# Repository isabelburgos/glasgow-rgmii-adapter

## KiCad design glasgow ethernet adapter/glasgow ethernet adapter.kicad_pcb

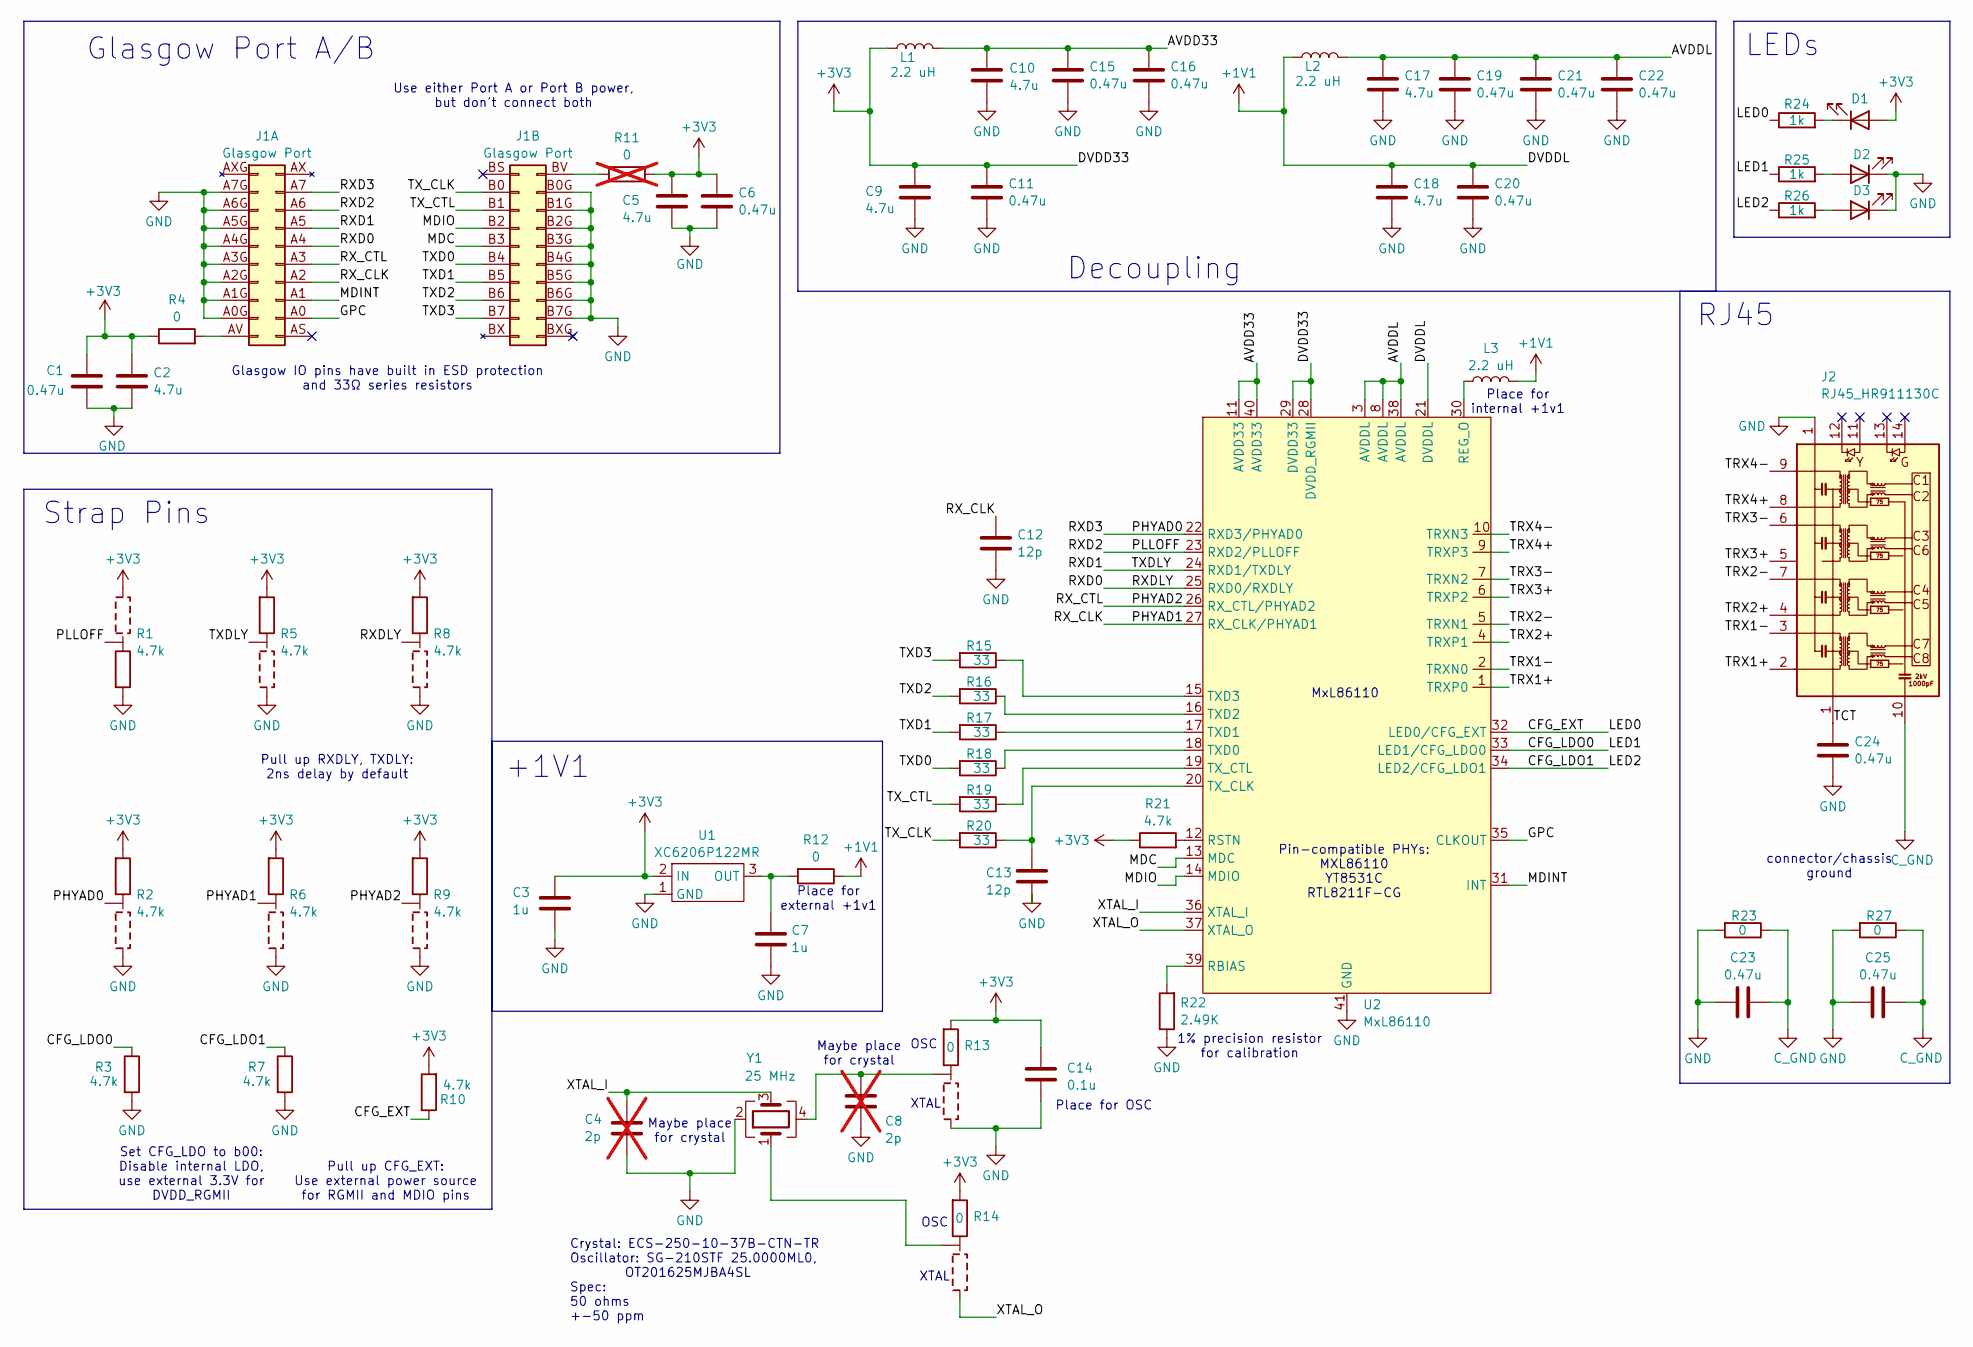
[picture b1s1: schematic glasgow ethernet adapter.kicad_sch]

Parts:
C1, C6, C11, C15, C16, C19, C20, C21, C22, C23, C24, C25: 0.47u; C_0402_1005Metric; JLC Part ID C967572
C2, C5, C9, C10, C17, C18: 4.7u; C_1206_3216Metric; JLC Part ID C29823
C3, C7: 1u; C_0603_1608Metric; JLC Part ID C1592
C4, C8: 2p; C_0402_1005Metric; not fitted
C12, C13: 12p; C_0402_1005Metric; JLC Part ID C1547
C14: 0.1u; C_0402_1005Metric; JLC Part ID C1525
D1: LED_0; D_0603_1608Metric; JLC Part ID C111340
D2: LED_1; D_0603_1608Metric; JLC Part ID C83904
D3: LED_2; D_0603_1608Metric; JLC Part ID C2977076
J1: Glasgow Port; Glasgow; JLC Part ID C124419
J2: RJ45_HR911130C; HR911130C_HAN; JLC Part ID C50933
L1, L2, L3: 2.2 uH; L_0603_1608Metric; JLC Part ID C17305
R1, R2, R5, R6, R8, R9: 4.7k; R-3-Way_0402_1005Metric; JLC Part ID C25900
R3, R7, R10, R21: 4.7k; R_0402_1005Metric; JLC Part ID C25900
R4: 0; R_0603_1608Metric; JLC Part ID C17168
R11: 0; R_0603_1608Metric; JLC Part ID C21189; not fitted
R12: 0; R_0603_1608Metric; JLC Part ID C15402
R13, R14: 0; R-3-Way_0402_1005Metric; JLC Part ID C17168
R15, R16, R17, R18, R19, R20: 33; R_0402_1005Metric; JLC Part ID C25105
R22: 2.49K; R_0402_1005Metric; JLC Part ID C102924
R23, R27: 0; R_0402_1005Metric; JLC Part ID C17168
R24, R25, R26: 1k; R_0402_1005Metric; JLC Part ID C173697
U1: XC6206P122MR; SOT-23; JLC Part ID C2827649
U2: MxL86110; QFN-40-1EP_5x5mm_P0.4mm_EP3.8x3.8mm; JLC Part ID C187932
Y1: 25 MHz; XTAL_ECS-160-9-37-CKM-TR; JLC Part ID C669080

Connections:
+1V1: C18.1, C20.1, L2.1, L3.2, R12.1, U2.21 (DVDDL)
+3V3: C1.1, C2.1, C3.1, C5.1, C6.1, C9.1, C11.1, C14.1, D1.2 (A), L1.1, R1.3, R2.1, R4.1, R5.1, R6.1, R8.1, R9.1, R10.2, R11.1, R13.1, R14.1, R21.1, U1.2 (IN), U2.28 (DVDD_RGMII), U2.29 (DVDD33)
/AVDD33: C10.1, C15.1, C16.1, L1.2, U2.11 (AVDD33), U2.40 (AVDD33)
/AVDDL: C17.1, C19.1, C21.1, C22.1, L2.2, U2.3 (AVDDL), U2.8 (AVDDL), U2.38 (AVDDL)
/CFG_EXT: R10.1, R24.1, U2.32 (LED0/CFG_EXT)
/CFG_LDO0: R3.1, R25.1, U2.33 (LED1/CFG_LDO0)
/CFG_LDO1: R7.1, R26.1, U2.34 (LED2/CFG_LDO1)
/GPC: J1.A0, U2.35 (CLKOUT)
/MDC: J1.B3, U2.13 (MDC)
/MDINT: J1.A1, U2.31 (INT)
/MDIO: J1.B2, U2.14 (MDIO)
/PHYAD0: J1.A7, R2.2, U2.22 (RXD3/PHYAD0)
/PHYAD1: C12.1, J1.A2, R6.2, U2.27 (RX_CLK/PHYAD1)
/PHYAD2: J1.A3, R9.2, U2.26 (RX_CTL/PHYAD2)
/PLLOFF: J1.A6, R1.2, U2.23 (RXD2/PLLOFF)
/RXD0: J1.A4, R8.2, U2.25 (RXD0/RXDLY)
/RXD1: J1.A5, R5.2, U2.24 (RXD1/TXDLY)
/TRX1+: J2.2 (0+), U2.1 (TRXP0)
/TRX1-: J2.3 (0-), U2.2 (TRXN0)
/TRX2+: J2.4 (1+), U2.4 (TRXP1)
/TRX2-: J2.7 (1-), U2.5 (TRXN1)
/TRX3+: J2.5 (2+), U2.6 (TRXP2)
/TRX3-: J2.6 (2-), U2.7 (TRXN2)
/TRX4+: J2.8 (3+), U2.9 (TRXP3)
/TRX4-: J2.9 (3-), U2.10 (TRXN3)
/TXD0: J1.B4, R18.2
/TXD1: J1.B5, R17.2
/TXD2: J1.B6, R16.2
/TXD3: J1.B7, R15.2
/TX_CLK: J1.B0, R20.2
/TX_CTL: J1.B1, R19.2
/XTAL_I: C4.1, U2.36 (XTAL_I), Y1.3
/XTAL_O: R14.3, U2.37 (XTAL_O)
C_GND: C23.1, C25.1, J2.10 (SH), R23.1, R27.1
unnamed: C8.1, R13.2, Y1.4
unnamed: D1.1 (K), R24.2
unnamed: D2.2 (A), R25.2
unnamed: D3.2 (A), R26.2
unnamed: J1.AV, R4.2
unnamed: J1.BV, R11.2
unnamed: R14.2, Y1.1
unnamed: C7.1, R12.2, U1.3 (OUT)
unnamed: R22.2, U2.39 (RBIAS)
unnamed: L3.1, U2.30 (REG_O)
unnamed: R21.2, U2.12 (RSTN)
unnamed: R18.1, U2.18 (TXD0)
unnamed: R17.1, U2.17 (TXD1)
unnamed: R16.1, U2.16 (TXD2)
unnamed: R15.1, U2.15 (TXD3)
unnamed: C13.1, R20.1, U2.20 (TX_CLK)
unnamed: R19.1, U2.19 (TX_CTL)

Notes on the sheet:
Place for external +1v1
OSC
Strap Pins
Maybe place for crystal
MxL86110
Pull up RXDLY, TXDLY: 2ns delay by default
Use either Port A or Port B power, but don't connect both
connector/chassis ground
Set CFG_LDO to b00: Disable internal LDO, use external 3.3V for DVDD_RGMII
Pull up CFG_EXT: Use external power source for RGMII and MDIO pins
+1V1
XTAL
Place for OSC
1% precision resistor for calibration
Decoupling
Pin-compatible PHYs: MXL86110 YT8531C RTL8211F-CG
Place for internal +1v1
Glasgow Port A/B
RJ45
Glasgow IO pins have built in ESD protection and 33Ω series resistors
Crystal: ECS-250-10-37B-CTN-TR Oscillator: SG-210STF 25.0000ML0, OT201625MJBA4SL Spec: 50 ohms +-50 ppm
LEDs

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
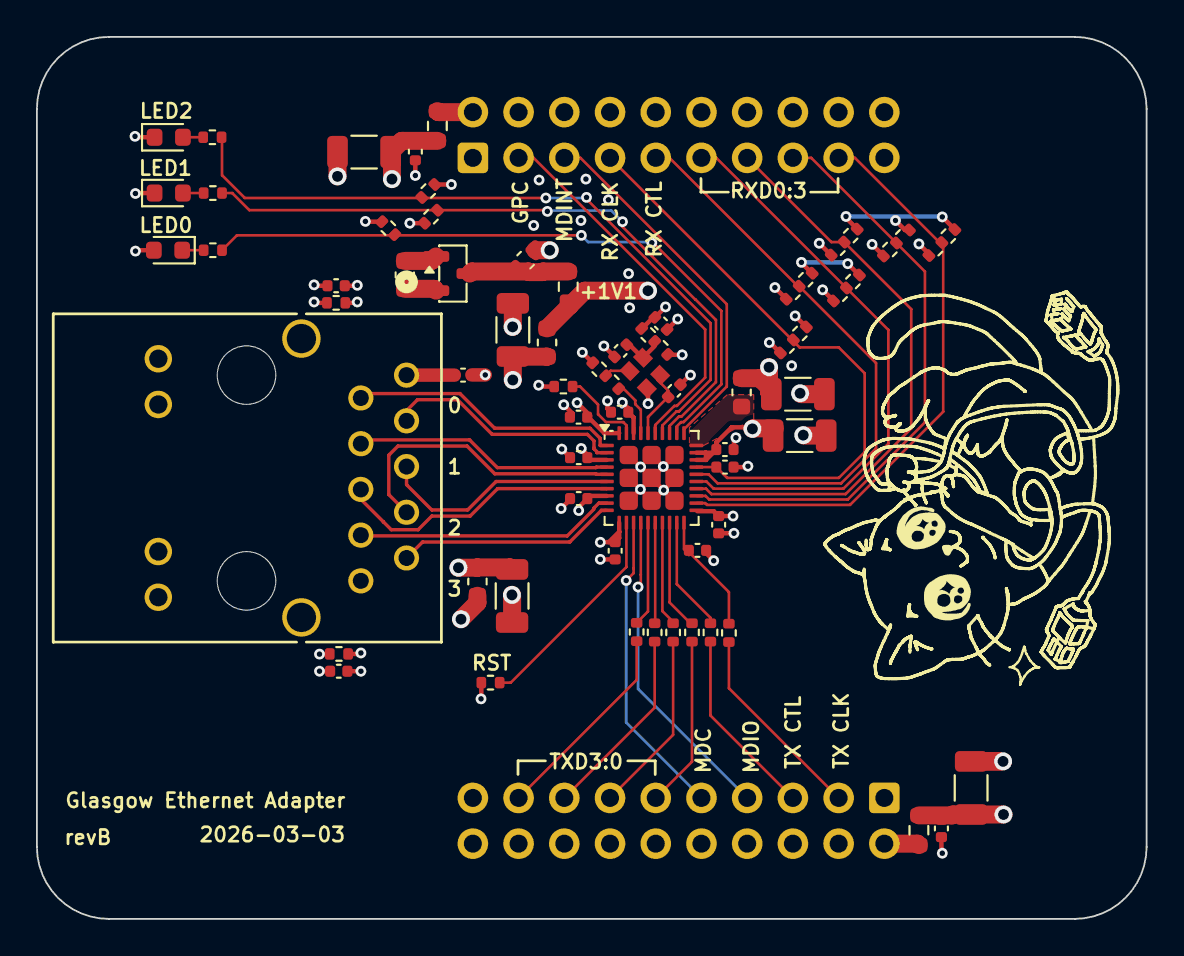
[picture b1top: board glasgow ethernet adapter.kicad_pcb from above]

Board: 4 copper layers, 61.7 x 49.0 mm, 63 parts (0 on the bottom side), 53 nets.

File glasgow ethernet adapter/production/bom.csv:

Designator,Footprint,Quantity,Value,JLC Part #
"C1, C11, C15, C16, C19, C20, C21, C22, C23, C24, C25, C6",0402,12,0.47u,C967572
"C10, C17, C18, C2, C5, C9",1206,6,4.7u,C29823
"C12, C13",0402,2,12p,C1547
C14,0402,1,0.1u,C1525
"C3, C7",0603,2,1u,C1592
D1,0603,1,LED_0,C111340
D2,0603,1,LED_1,C83904
D3,0603,1,LED_2,C2977076
J1A,Conn_2x10,1,B-2200S20P-B120,C124419
J1B,Conn_2x10,1,B-2200S20P-B120,C124419
J2,HR911130C_HAN,1,RJ45_HR911130C,C50933
"L1, L2, L3",0603,3,2.2 uH,C17305
"R1, R2, R5, R6, R8, R9",R-3-Way_0402_1005Metric,6,4.7k,C25900
"R10, R21, R3, R7",0402,4,4.7k,C25900
"R12, R4",0603,2,0,C15402
"R13, R14",R-3-Way_0402_1005Metric,2,0,C17168
"R15, R16, R17, R18, R19, R20",0402,6,33,C25105
R22,0402,1,2.49K,C102924
"R23, R27",0402,2,0,C17168
"R24, R25, R26",0402,3,1k,C173697
U1,SOT-23,1,XC6206P122MR,C2827649
U2,QFN-40-1EP_5x5mm_P0.4mm_EP3.8x3.8mm,1,MxL86110,C187932
Y1,XTAL_ECS-160-9-37-CKM-TR,1,25 MHz,C669080

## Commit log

2024-04-22 move datasheets into their own folder
2024-04-22 summarize what's been learned so far
2024-04-22 fix markdown links
2024-05-25 add additional pinouts
2024-05-25 fix table formatting
2024-05-25 add LAN8820
2024-05-25 add transformer + protoype layout for transformer
2024-05-25 add link to KSZ9031RNZ die reference photo
2025-06-25 wip - connect MDC, add crystal
2025-06-25 wip - add 4-pair RJ45, switch to 4 layers
2025-06-26 wip - add silkscreen
2025-06-26 move strap resistors closer to PHY
2025-06-26 length match RGMII traces
2025-06-26 length match diff pairs
2025-06-27 misc fixes and DRC
2025-07-01 add capacitors to crystal
2025-07-02 tweaks
2025-07-04 swap and re-route pairs
2025-07-04 simply ground transformer center tap
2025-07-04 squash back to 2 layers
2025-07-04 add oscillator compatible layout
2025-07-05 go back to 4 layers
2025-07-05 redo power + decoupling
2025-07-05 remove configurable pulls on LEDs
2025-07-06 move things around
2025-07-07 increase fab tolerances, DRC fixes
2025-07-08 export fab outputs, add note on parts sourcing
2026-01-16 add license (same as glasgow)
2026-01-27 un-swap pins
2026-01-27 add RX_CTL silkscreen label
2026-01-27 add 1v1 regulator
2026-02-09 swap MDC+MDIO with TXD0:3
2026-02-09 individually identify LEDs (to assign colors in BOM)
2026-02-10 add Cout to +1v1, add to resistor silk
2026-02-10 add JLC part numbers
2026-02-23 replace LDO with one from JLC, renumber schematic
2026-02-23 export JLC fab outputs
2026-03-03 replace RJ45 connector with one more available on JLC
2026-03-03 Add revB silkscreen text
